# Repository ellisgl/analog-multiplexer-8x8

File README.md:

Analog Multiplexer using the 74xx4051 DIP package (KiCad)
=========================================================

64 inputs, 8 outputs, 3 bit address selects a column (0-7) and outputs 8 row values.

PCB is under 100mm x 100mm, so cheap PCBs from certain PCB manufactures.

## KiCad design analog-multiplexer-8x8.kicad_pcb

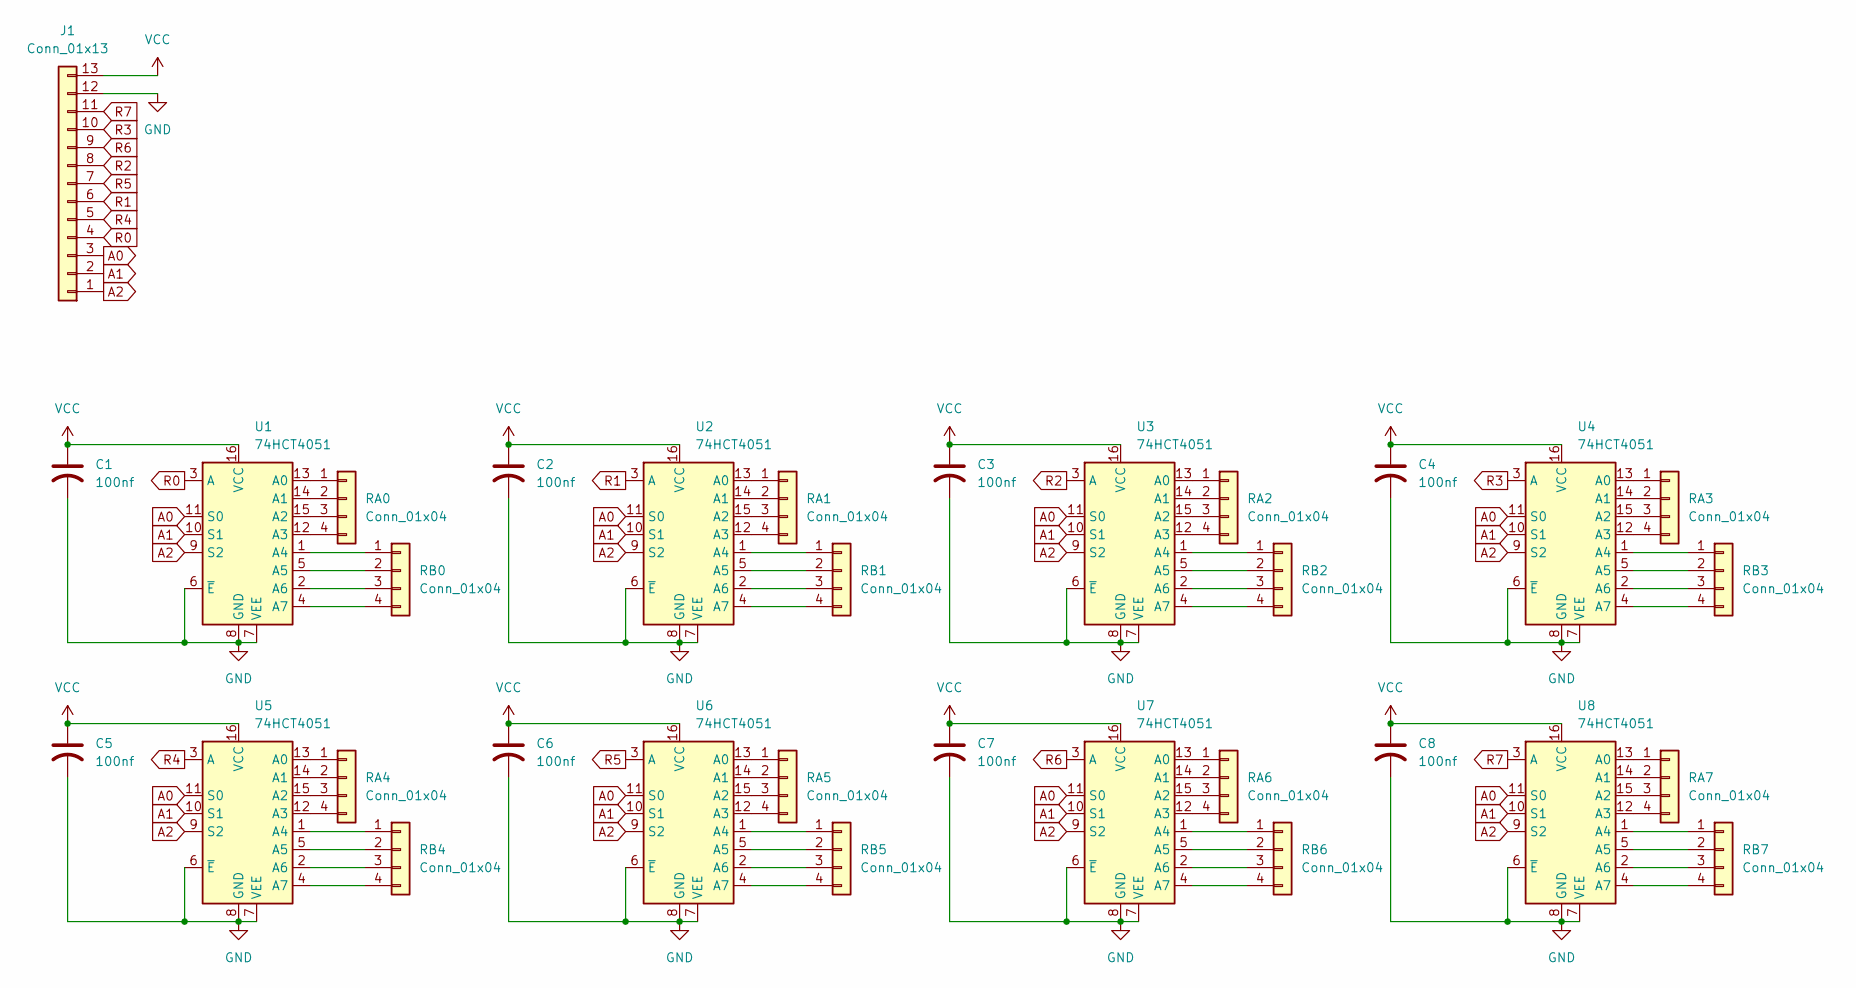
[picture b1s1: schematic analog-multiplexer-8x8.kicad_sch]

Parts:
C1, C2, C3, C4, C5, C6, C7, C8: 100nf; C_1206_3216Metric
J1: Conn_01x13; PinHeader_1x13_P2.54mm_Vertical
RA0, RA1, RA2, RA3, RA4, RA5, RA6, RA7: Conn_01x04; PinHeader_1x04_P2.54mm_Vertical; JLCPBCPartNumber C2691448
RB0, RB1, RB2, RB3, RB4, RB5, RB6, RB7: Conn_01x04; PinHeader_1x04_P2.54mm_Vertical; JLCPBCPartNumber C2691448
U1, U2, U3, U4, U5, U6, U7, U8: 74HCT4051; DIP-16_W7.62mm_LongPads

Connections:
A0: J1.3, U1.11 (S0), U2.11 (S0), U3.11 (S0), U4.11 (S0), U5.11 (S0), U6.11 (S0), U7.11 (S0), U8.11 (S0)
A1: J1.2, U1.10 (S1), U2.10 (S1), U3.10 (S1), U4.10 (S1), U5.10 (S1), U6.10 (S1), U7.10 (S1), U8.10 (S1)
A2: J1.1, U1.9 (S2), U2.9 (S2), U3.9 (S2), U4.9 (S2), U5.9 (S2), U6.9 (S2), U7.9 (S2), U8.9 (S2)
GND: C1.2, C2.2, C3.2, C4.2, C5.2, C6.2, C7.2, C8.2, J1.12, U1.6 (~E), U1.7 (VEE), U1.8 (GND), U2.6 (~E), U2.7 (VEE), U2.8 (GND), U3.6 (~E), U3.7 (VEE), U3.8 (GND), U4.6 (~E), U4.7 (VEE), U4.8 (GND), U5.6 (~E), U5.7 (VEE), U5.8 (GND), U6.6 (~E), U6.7 (VEE), U6.8 (GND), U7.6 (~E), U7.7 (VEE), U7.8 (GND), U8.6 (~E), U8.7 (VEE), U8.8 (GND)
unnamed: RA0.1, U1.13 (A0)
unnamed: RA0.2, U1.14 (A1)
unnamed: RA0.3, U1.15 (A2)
unnamed: RA0.4, U1.12 (A3)
unnamed: RA1.1, U2.13 (A0)
unnamed: RA1.2, U2.14 (A1)
unnamed: RA1.3, U2.15 (A2)
unnamed: RA1.4, U2.12 (A3)
unnamed: RA2.1, U3.13 (A0)
unnamed: RA2.2, U3.14 (A1)
unnamed: RA2.3, U3.15 (A2)
unnamed: RA2.4, U3.12 (A3)
unnamed: RA3.1, U4.13 (A0)
unnamed: RA3.2, U4.14 (A1)
unnamed: RA3.3, U4.15 (A2)
unnamed: RA3.4, U4.12 (A3)
unnamed: RA4.1, U5.13 (A0)
unnamed: RA4.2, U5.14 (A1)
unnamed: RA4.3, U5.15 (A2)
unnamed: RA4.4, U5.12 (A3)
unnamed: RA5.1, U6.13 (A0)
unnamed: RA5.2, U6.14 (A1)
unnamed: RA5.3, U6.15 (A2)
unnamed: RA5.4, U6.12 (A3)
unnamed: RA6.1, U7.13 (A0)
unnamed: RA6.2, U7.14 (A1)
unnamed: RA6.3, U7.15 (A2)
unnamed: RA6.4, U7.12 (A3)
unnamed: RA7.1, U8.13 (A0)
unnamed: RA7.2, U8.14 (A1)
unnamed: RA7.3, U8.15 (A2)
unnamed: RA7.4, U8.12 (A3)
unnamed: RB0.1, U1.1 (A4)
unnamed: RB0.2, U1.5 (A5)
unnamed: RB0.3, U1.2 (A6)
unnamed: RB0.4, U1.4 (A7)
unnamed: RB1.1, U2.1 (A4)
unnamed: RB1.2, U2.5 (A5)
unnamed: RB1.3, U2.2 (A6)
unnamed: RB1.4, U2.4 (A7)
unnamed: RB2.1, U3.1 (A4)
unnamed: RB2.2, U3.5 (A5)
unnamed: RB2.3, U3.2 (A6)
unnamed: RB2.4, U3.4 (A7)
unnamed: RB3.1, U4.1 (A4)
unnamed: RB3.2, U4.5 (A5)
unnamed: RB3.3, U4.2 (A6)
unnamed: RB3.4, U4.4 (A7)
unnamed: RB4.1, U5.1 (A4)
unnamed: RB4.2, U5.5 (A5)
unnamed: RB4.3, U5.2 (A6)
unnamed: RB4.4, U5.4 (A7)
unnamed: RB5.1, U6.1 (A4)
unnamed: RB5.2, U6.5 (A5)
unnamed: RB5.3, U6.2 (A6)
unnamed: RB5.4, U6.4 (A7)
unnamed: RB6.1, U7.1 (A4)
unnamed: RB6.2, U7.5 (A5)
unnamed: RB6.3, U7.2 (A6)
unnamed: RB6.4, U7.4 (A7)
unnamed: RB7.1, U8.1 (A4)
unnamed: RB7.2, U8.5 (A5)
unnamed: RB7.3, U8.2 (A6)
unnamed: RB7.4, U8.4 (A7)
R0: J1.4, U1.3 (A)
R1: J1.6, U2.3 (A)
R2: J1.8, U3.3 (A)
R3: J1.10, U4.3 (A)
R4: J1.5, U5.3 (A)
R5: J1.7, U6.3 (A)
R6: J1.9, U7.3 (A)
R7: J1.11, U8.3 (A)
VCC: C1.1, C2.1, C3.1, C4.1, C5.1, C6.1, C7.1, C8.1, J1.13, U1.16 (VCC), U2.16 (VCC), U3.16 (VCC), U4.16 (VCC), U5.16 (VCC), U6.16 (VCC), U7.16 (VCC), U8.16 (VCC)

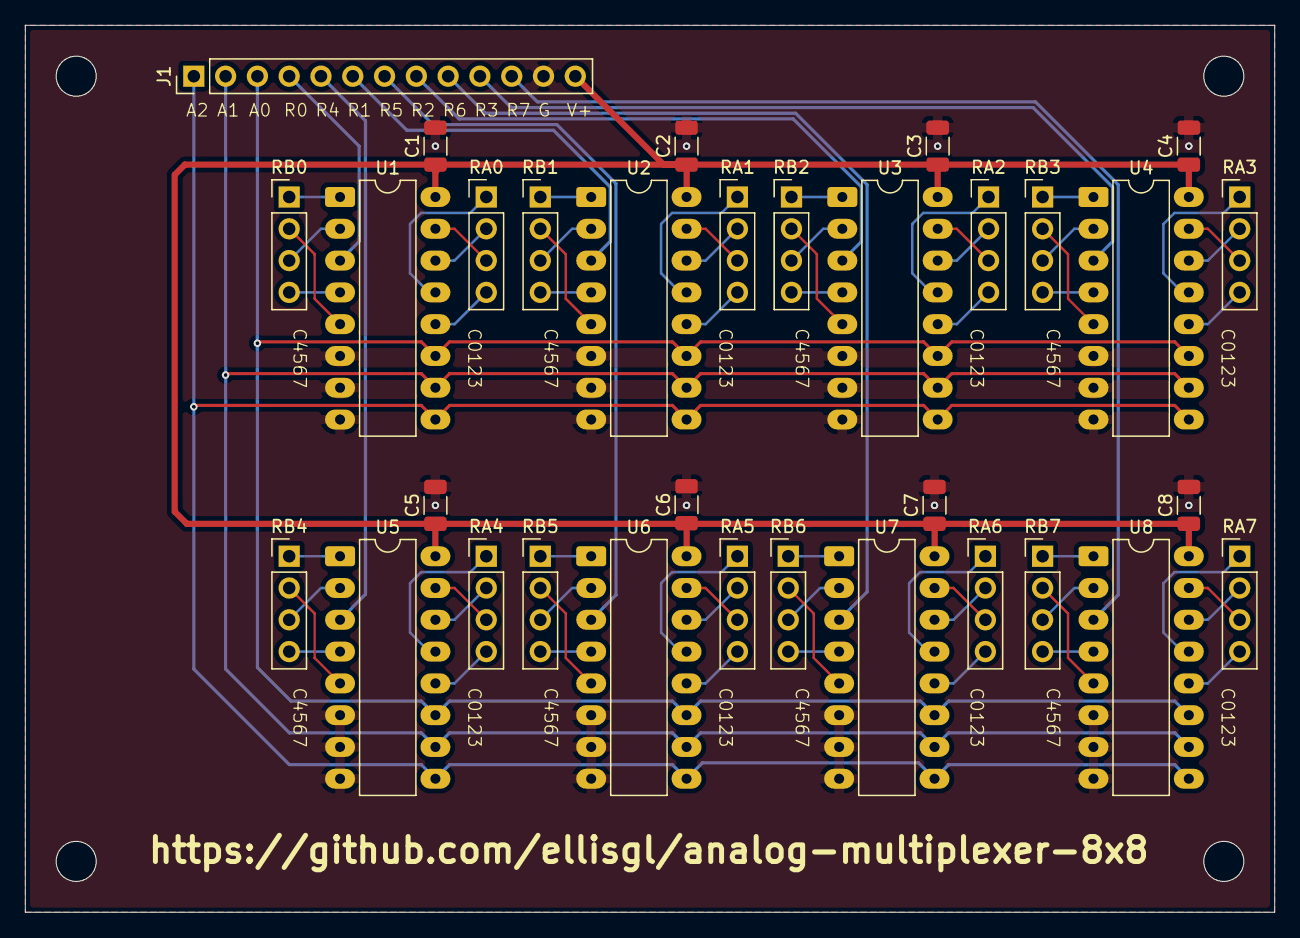
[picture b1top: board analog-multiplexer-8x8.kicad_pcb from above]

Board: 2 copper layers, 99.8 x 70.9 mm, 33 parts (0 on the bottom side), 77 nets.

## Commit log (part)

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2018-05-11 Initial Commit.
2018-05-11 Removed backup file...
2018-05-11 Added PDF of schematic.
2018-05-15 Changed 8mil tracks to 10mil.
2018-05-16 Removed backup file
2018-05-16 Updated gerbers.
2018-05-16 Added license.
2018-05-16 Fixed edge cuts on PCB.
2018-05-24 Shrunk PCB to under 100mm
2018-05-27 Removing backup file
2018-05-28 Moar docs!
2018-06-11 Removed via on power trace and re-used through-hole pin hole. 4 vias placed on the board, 4 vias places on the board, take one out, pass it around, 3 vias left on the board.
2019-09-14 Rename LICENSE to LICENSE.BSD
